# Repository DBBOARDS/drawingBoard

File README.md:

# drawingBoard
Arduino Drawing Board Eagle files

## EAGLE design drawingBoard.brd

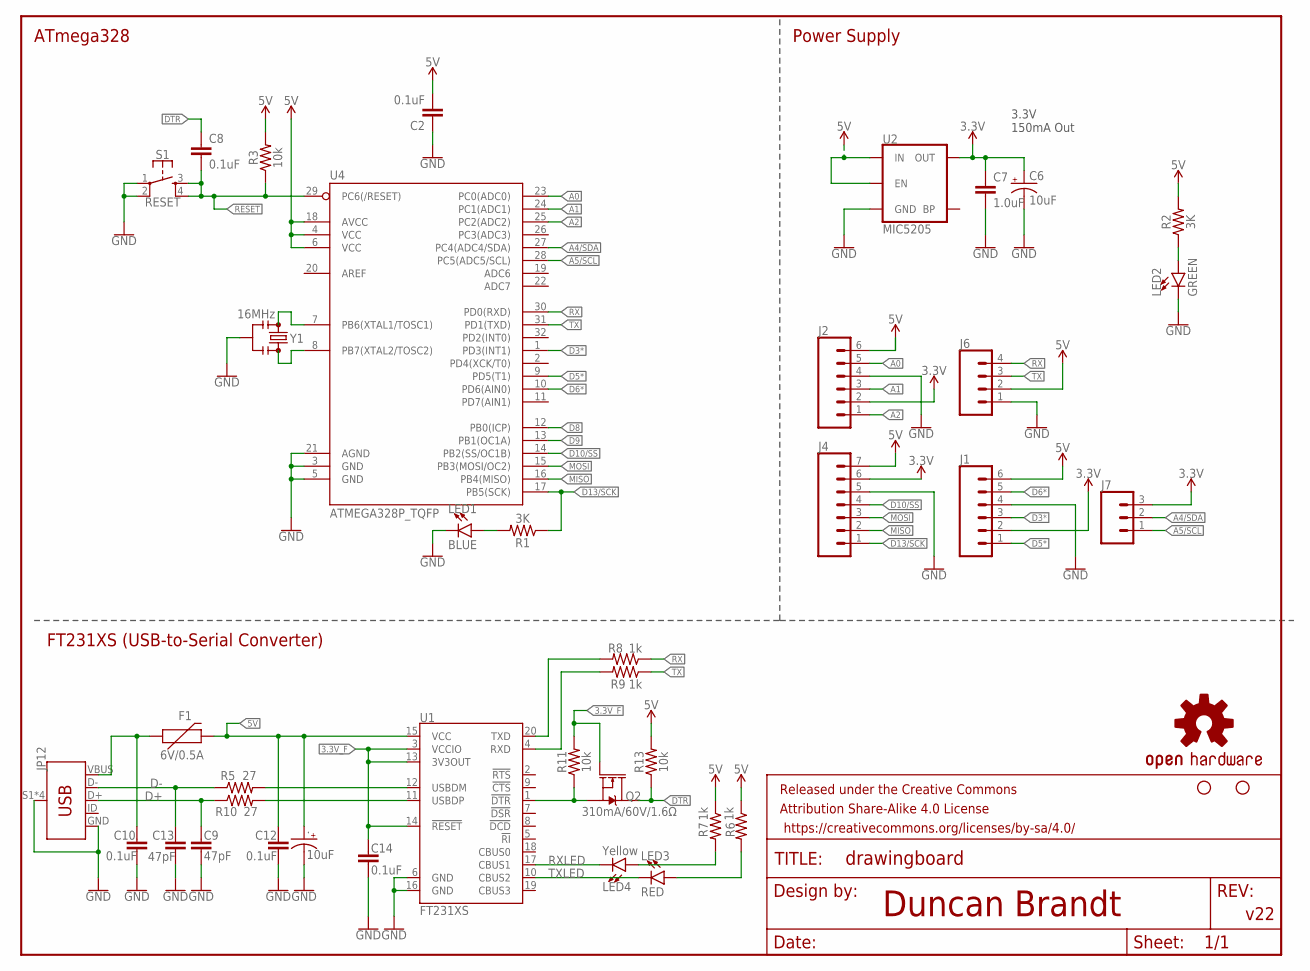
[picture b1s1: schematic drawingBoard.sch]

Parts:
.: 10uF; EIA3216
C2, C8, C10, C12, C14: 0.1uF; 0603
C6: 10uF; EIA3216
C7: 1.0uF; 0603
C9, C13: 47pF; 0603
F1: 6V/0.5A; 1206
FRAME2: FRAME-LETTER; CREATIVE_COMMONS
J1, J2: CONN_06SILK_FEMALE_PTH; 1X06
J4: CONN_07; 1X07
J6: CONN_04; 1X04
J7: CONN_03; 1X03
JP3, JP6: STAND-OFF
JP12: USB_MINI-B_SMT; USB-MINIB
LED1: BLUE; LED-1206
LED2: GREEN; LED-1206
LED3: RED; LED-1206
LED4: Yellow; LED-1206
Q2: 310mA/60V/1.6Ω; SOT323
R1, R2: 3K; 0603
R3, R11, R13: 10k; 0603
R5, R10: 27; 0603
R6, R7, R8, R9: 1k; 0603
S1: RESET; TACTILE_SWITCH_SMD_5.2MM
U1: FT231XS; SSOP20_L
U2: MIC5205; SOT23-5
U4: ATMEGA328P_TQFP; TQFP32-08
U$16: OSHW-LOGOS; OSHW-LOGO-S
Y1: 16MHz; RESONATOR-SMD-3.2X1.3

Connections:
3.3V: C6.+, C7.1, J1.2, J2.2, J4.6, J7.3, U2.5 (OUT)
3.3V_F: C14.1, Q2.1 (G), R11.2, U1.3 (VCCIO), U1.13 (3V3OUT), U1.14 (!RESET)
5V: ..+, C2.2, C12.1, F1.2, J1.6, J2.6, J4.7, J6.2, R2.2, R3.2, R6.1, R7.1, R13.2, U1.15 (VCC), U2.1 (IN), U2.3 (EN), U4.4 (VCC), U4.6 (VCC), U4.18 (AVCC)
A0: J2.5, U4.23 (PC0(ADC0))
A1: J2.3, U4.24 (PC1(ADC1))
A2: J2.1, U4.25 (PC2(ADC2))
A4/SDA: J7.2, U4.27 (PC4(ADC4/SDA))
A5/SCL: J7.1, U4.28 (PC5(ADC5/SCL))
D3*: J1.3, U4.1 (PD3(INT1))
D5*: J1.1, U4.9 (PD5(T1))
D6*: J1.5, U4.10 (PD6(AIN0))
D8: U4.12 (PB0(ICP))
D9: U4.13 (PB1(OC1A))
D10/SS: J4.4, U4.14 (PB2(SS/OC1B))
D13/SCK: J4.1, R1.1, U4.17 (PB5(SCK))
D+: C9.1, JP12.D+, R10.1
D-: C13.1, JP12.D-, R5.1
DTR: C8.1, Q2.3 (D), R13.1
FTDI_DTR: Q2.2 (S), R11.1, U1.1 (!DTR)
GND: ..-, C2.1, C6.-, C7.2, C9.2, C10.2, C12.2, C13.2, C14.2, J1.4, J2.4, J4.5, J6.1, JP12.GND, JP12.S1 (SHIELD), JP12.S2 (SHIELD), JP12.S3 (SHIELD), JP12.S4 (SHIELD), LED1.C, LED2.C, S1.1, S1.2, U1.6 (GND), U1.16 (GND), U2.2 (GND), U4.3 (GND), U4.5 (GND), U4.21 (AGND), Y1.2
MISO: J4.2, U4.16 (PB4(MISO))
MOSI: J4.3, U4.15 (PB3(MOSI/OC2))
unnamed: LED1.A, R1.2
unnamed: LED2.A, R2.1
unnamed: U4.7 (PB6(XTAL1/TOSC1)), Y1.1
unnamed: U4.8 (PB7(XTAL2/TOSC2)), Y1.3
unnamed: R5.2, U1.12 (USBDM)
unnamed: R10.2, U1.11 (USBDP)
unnamed: LED3.A, R6.2
unnamed: LED4.A, R7.2
RESET: C8.2, R3.1, S1.3, S1.4, U4.29 (PC6(/RESET))
RX: J6.4, R8.1, U4.30 (PD0(RXD))
RXD: R9.2, U1.4 (RXD)
RXLED: LED4.C, U1.17 (CBUS1)
TX: J6.3, R9.1, U4.31 (PD1(TXD))
TXD: R8.2, U1.20 (TXD)
TXLED: LED3.C, U1.10 (CBUS2)
VUSB: C10.1, F1.1, JP12.VBUS

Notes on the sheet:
Duncan Brandt
Power Supply
ATmega328
FT231XS (USB-to-Serial Converter)
3.3V 150mA Out
v22

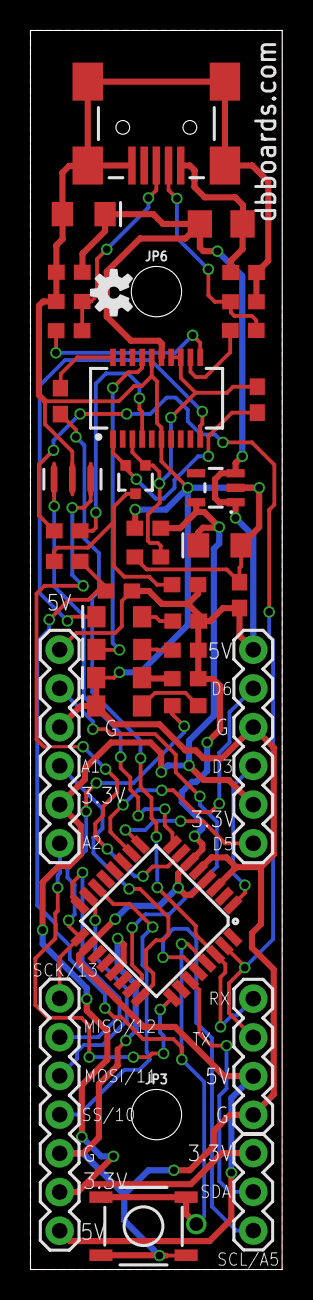
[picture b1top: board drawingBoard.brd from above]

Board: 2 copper layers, 16.5 x 81.3 mm, 43 parts (1 on the bottom side), 36 nets.

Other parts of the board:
U$7: OSHW-LOGOS; OSHW-LOGO-S

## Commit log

2017-11-14 Drawing Board Eagle Files
    These are the Eagle board and schematic files for DB Boards' Arduino driven Drawing Board.

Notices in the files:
parts and their libraries:
DB-CONN: Licensing: Creative Commons ShareAlike 4.0 International - https://creativecommons.org/licenses/by-sa/4.0
DB-SYMBOLS: Released under the Creative Commons Attribution Share-Alike 4.0 License
DB-SYMBOLS: https://creativecommons.org/licenses/by-sa/4.0
